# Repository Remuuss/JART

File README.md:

# JART PPS4 Reconnaissance des chiffres manuscrits utilisant l'intelligence artificielle (AI) avec l'apprentissage machine (Machine Learning)

## Voici la description de chacun des fichiers présent dans le projet.

BodyBase.stl : Fichier du modèle 3D du boitier.

BodyTop.stl : Fichier du modèle 3D du couvercle du boitier.

breakout.brd : Fichier du matricielle de la carte soeur.

breakout.sch : Fichier du schématique de la carte soeur.

draft.brd : Fichier du matricielle de la carte mère.

draft.sch : Fichier du schématique de la carte mère.

main.py : Fichier du code principal.

Cours PPS Projet_PPS4_V2.docx : Fichier du cahier de charge

PPS4_Base.gan, PPS4_S2.gan, PPS4_S3.gan, PPS4_S4.gan, PPS4_S5.gan : Échéancier modifier à chaque semaine (S2, S3, S4, S5).

Diagramme Fonctionnel.sch : Fichier du diagramme du fonctionnel du projet.

## Lien utilisé

Nous nous sommes inspirés de ce projet pour réaliser le nôtre : https://github.com/code2k13/rpipico_digit_classification/tree/main

Librairie utilisé pour la caméra (modifié) : https://github.com/namato/micropython-ov2640

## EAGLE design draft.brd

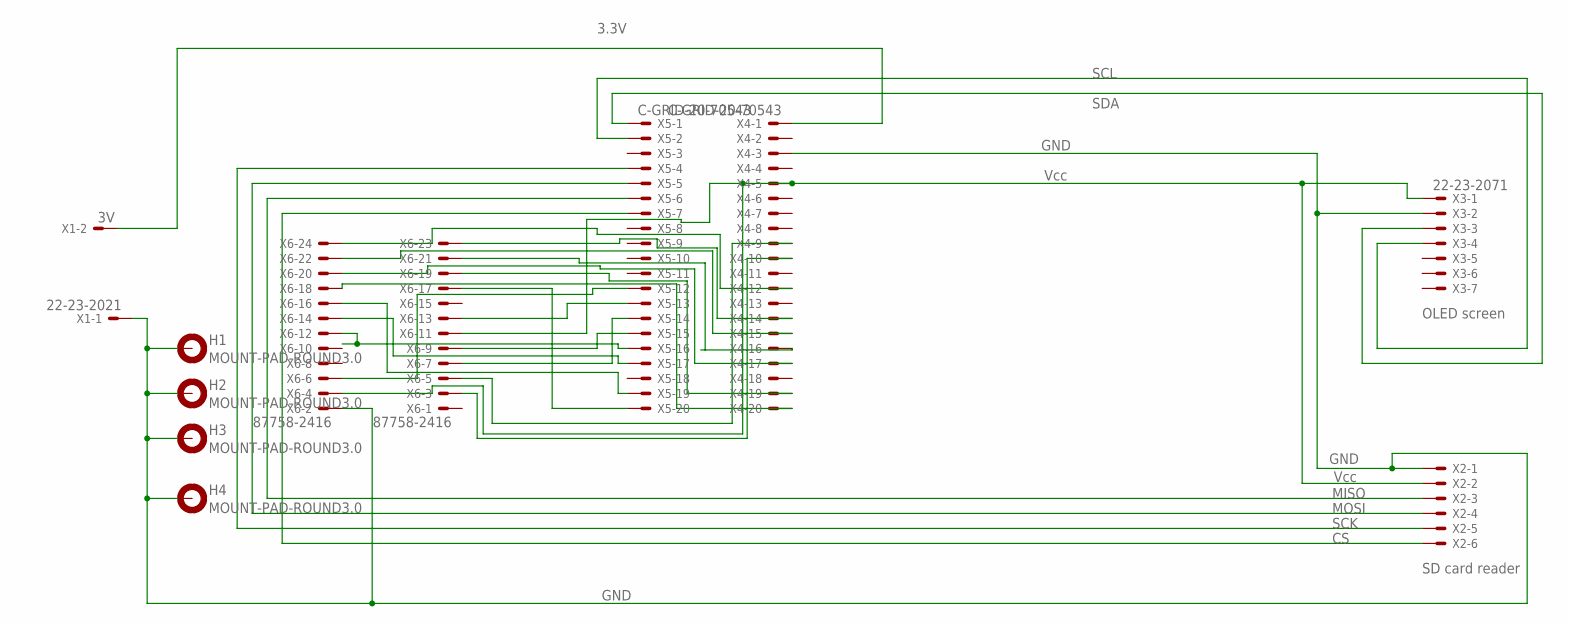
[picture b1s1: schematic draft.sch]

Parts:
H1, H2, H3, H4: MOUNT-PAD-ROUND3.0; 3,0-PAD
X1: 22-23-2021
X2: 22-23-2061
X3: 22-23-2071
X4, X5: C-GRID-20-70543; 70543-20
X6: 87758-2416

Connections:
GND: H1.B3,0, H2.B3,0, H3.B3,0, H4.B3,0, X1.1, X2.1, X3.2, X4.3, X6.2
unnamed: X5.17, X6.14
unnamed: X2.2, X3.1, X4.5, X6.4, X6.11
unnamed: X3.4, X5.2
unnamed: X4.10, X6.3
unnamed: X2.5, X5.4
unnamed: X2.4, X5.5
unnamed: X2.3, X5.6
unnamed: X2.6, X5.7
unnamed: X4.9, X6.5
unnamed: X1.2, X4.1
unnamed: X3.3, X5.1
unnamed: X5.12, X6.6
unnamed: X5.14, X6.7
unnamed: X5.15, X6.9
unnamed: X5.16, X6.12
unnamed: X4.20, X6.18
unnamed: X5.19, X6.16
unnamed: X5.13, X6.13
unnamed: X5.20, X6.17
unnamed: X4.19, X6.19
unnamed: X4.17, X6.20
unnamed: X4.16, X6.21
unnamed: X4.15, X6.22
unnamed: X4.14, X6.23
unnamed: X4.12, X6.24

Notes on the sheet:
OLED screen
SD card reader
GND
3.3V
SDA
SCL
Vcc
MISO
MOSI
SCK

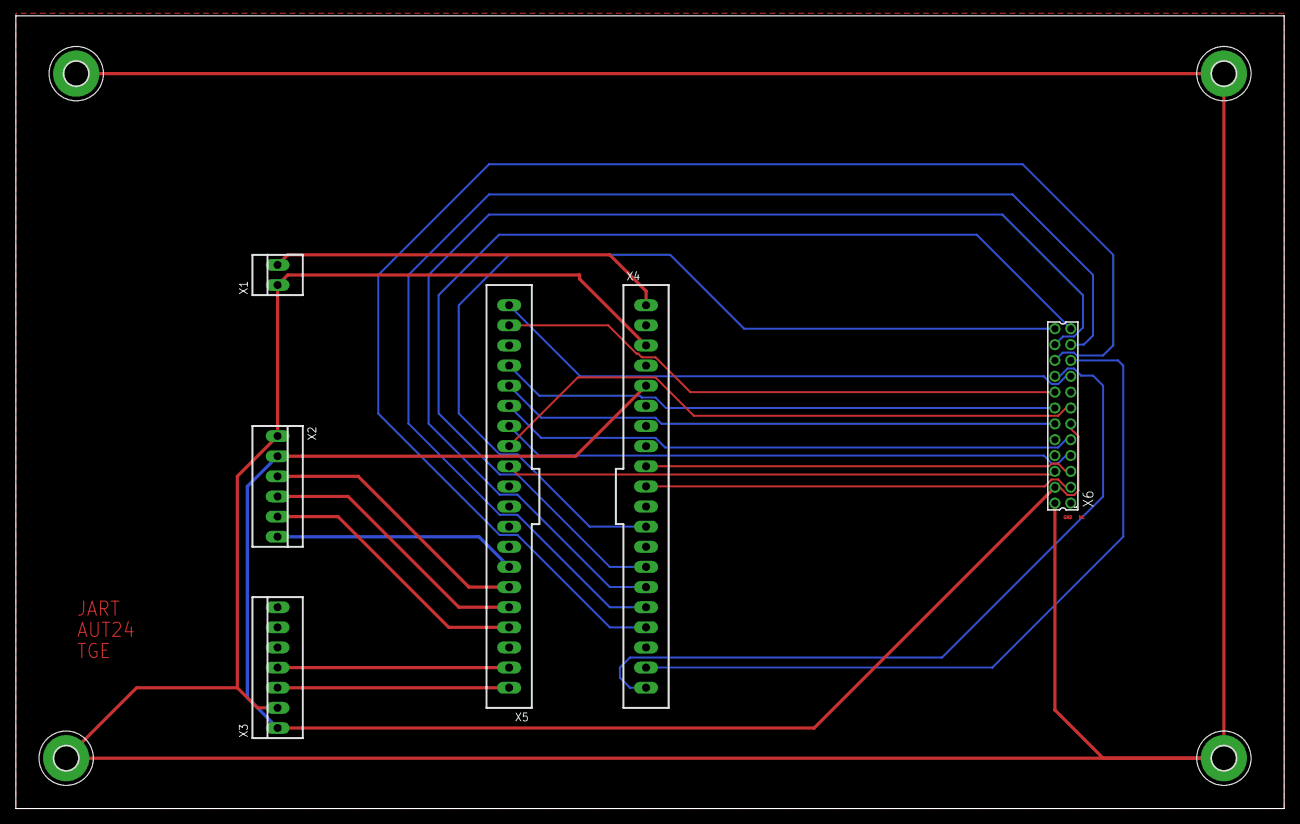
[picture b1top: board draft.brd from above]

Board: 2 copper layers, 160.0 x 100.0 mm, 10 parts (0 on the bottom side), 26 nets.

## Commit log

2024-11-04 premier test :)
2024-11-04 test
2024-11-18 Code principal
2024-11-20 Create README.md
    Explication des fichiers dans le github
2024-11-20 Image du diagramme fonctionnel
2024-11-20 Create boitier 3D
2024-11-20 Create Librairie
2024-11-20 Modèle machine learning
2024-11-20 Create ov2640
2024-11-20 Rename ReadMe to README.md
